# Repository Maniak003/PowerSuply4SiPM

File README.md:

# PowerSuply4SiPM
Power source for 30v

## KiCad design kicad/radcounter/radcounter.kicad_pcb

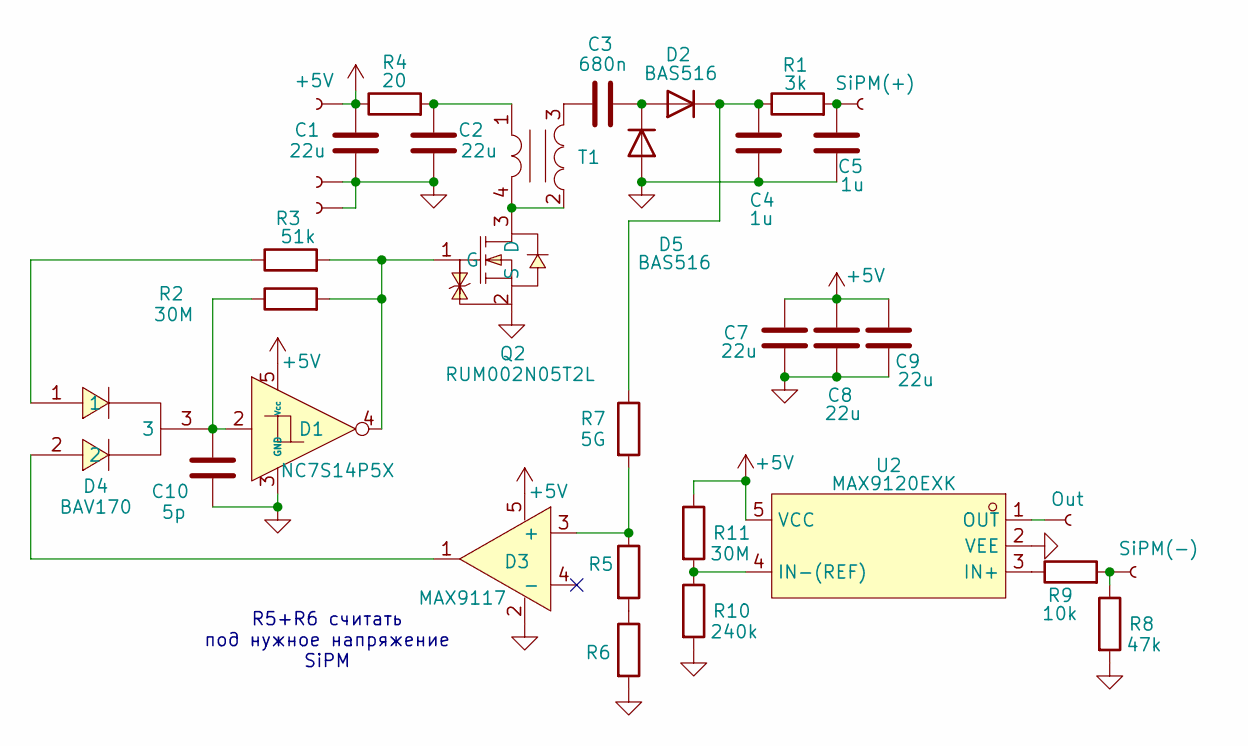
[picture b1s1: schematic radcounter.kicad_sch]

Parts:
C1, C2, C7, C8, C9: 22u; C_0402_1005Metric
C3: 680n; C_0402_1005Metric
C4, C5: 1u; C_0603_1608Metric
C10: 5p; C_0402_1005Metric
D1: NC7S14P5X; SC-70-5_L2.1-W1.3-P0.65-LS2.2-BR
D2, D5: BAS516; D_SOD-523
D3: MAX9117; SC-70-5_L2.1-W1.3-P0.65-LS2.2-BR
D4: BAV170; SOT-23_L2.9-W1.3-P1.90-LS2.4-BR; LCSC Part C68970
J1: SiPM(+); ConnMini
J2: SiPM(-); ConnMini
J3: Out; ConnMini
J4, J5, J6: Conn; ConnMini
Q2: RUM002N05T2L; SOT-723-3_L1.2-W0.8-LS1.20-BR; LCSC Part C510347
R1: 3k; R_0402_1005Metric
R2, R11: 30M; R_0402_1005Metric
R3: 51k; R_0402_1005Metric
R4: 20; R_0402_1005Metric
R5: 300k; R_0402_1005Metric
R6: 10M; R_0402_1005Metric
R7: 5G; R_1206_3216Metric
R8: 47k; R_0402_1005Metric
R9: 10k; R_0402_1005Metric
R10: 240k; R_0402_1005Metric
T1: ATB322515-0110-T000; XFMR-SMD_ATB322515-0110-T000; LCSC Part C415291
U2: MAX9120EXK; SC-70-5_L2.0-W1.3-P0.65-LS2.1-BL; LCSC Part C3658301

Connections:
+5V: C1.1, C7.2, C8.2, C9.2, D1.5 (Vcc), D3.5, J4.1, R4.1, R11.1, U2.5 (VCC)
GND: C1.2, C2.2, C4.1, C5.1, C7.1, C8.1, C9.1, C10.1, D1.3 (GND), D3.2, D5.2 (A), J5.1, J6.1, Q2.2 (S), R6.2, R8.2, R10.2, U2.2 (VEE)
unnamed: C2.1, R4.2, T1.1
unnamed: C3.1, T1.3
unnamed: C5.2, J1.1, R1.2
unnamed: C10.2, D1.2, D4.3, R2.1
unnamed: C3.2, D2.2 (A), D5.1 (K)
unnamed: C4.2, D2.1 (K), R1.1, R7.1
unnamed: D3.3 (+), R5.1, R7.2
unnamed: D3.1, D4.2
unnamed: D4.1, R3.1
unnamed: J2.1, R8.1, R9.2
unnamed: Q2.3 (D), T1.2, T1.4
unnamed: D1.4, Q2.1 (G), R2.2, R3.2
unnamed: R5.2, R6.1
unnamed: R9.1, U2.3 (IN+)
unnamed: R10.1, R11.2, U2.4 (IN-(REF))
unnamed: J3.1, U2.1 (OUT)

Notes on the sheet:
R5+R6 считать под нужное напряжение SiPM

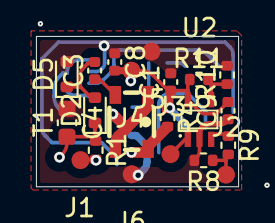
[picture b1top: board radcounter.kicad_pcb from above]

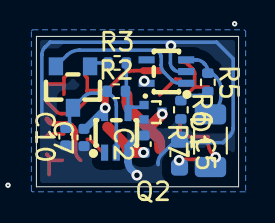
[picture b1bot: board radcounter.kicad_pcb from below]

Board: 2 copper layers, 11.2 x 8.4 mm, 34 parts (13 on the bottom side), 18 nets.

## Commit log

2026-01-03 удалено: kicad/radcounter/~radcounter.kicad_pcb.lck
2026-01-03 удалено: kicad/radcounter/radcounter-backups/radcounter-2025-12-29_170945.zip изменено: kicad/radcounter/radcounter.kicad_pcb
2026-01-03 удалено: kicad/radcounter/radcounter-backups/radcounter-2025-12-29_171823.zip удалено: kicad/radcounter/radcounter-backups/radcounter-2026-01-03_121429.zip изменено: kicad/radcounter/radcounter.kicad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
2026-01-03 новый файл: Documents/16x80-2.png новый файл: Documents/not-load.png изменено: kicad/radcounter/gerber/radcounter.drl удалено: kicad/radcounter/gerber/radcounter_T01_0.20mm.gcode удалено: kicad/radco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
2026-01-03 изменено: kicad/radcounter/radcounter.kicad_pcb изменено: kicad/radcounter/radcounter.kicad_prl
2026-01-03 новый файл: Documents/counter20x80.png удалено: kicad/radcounter/#auto_saved_files# удалено: kicad/radcounter/~radcounter.kicad_sch.lck
